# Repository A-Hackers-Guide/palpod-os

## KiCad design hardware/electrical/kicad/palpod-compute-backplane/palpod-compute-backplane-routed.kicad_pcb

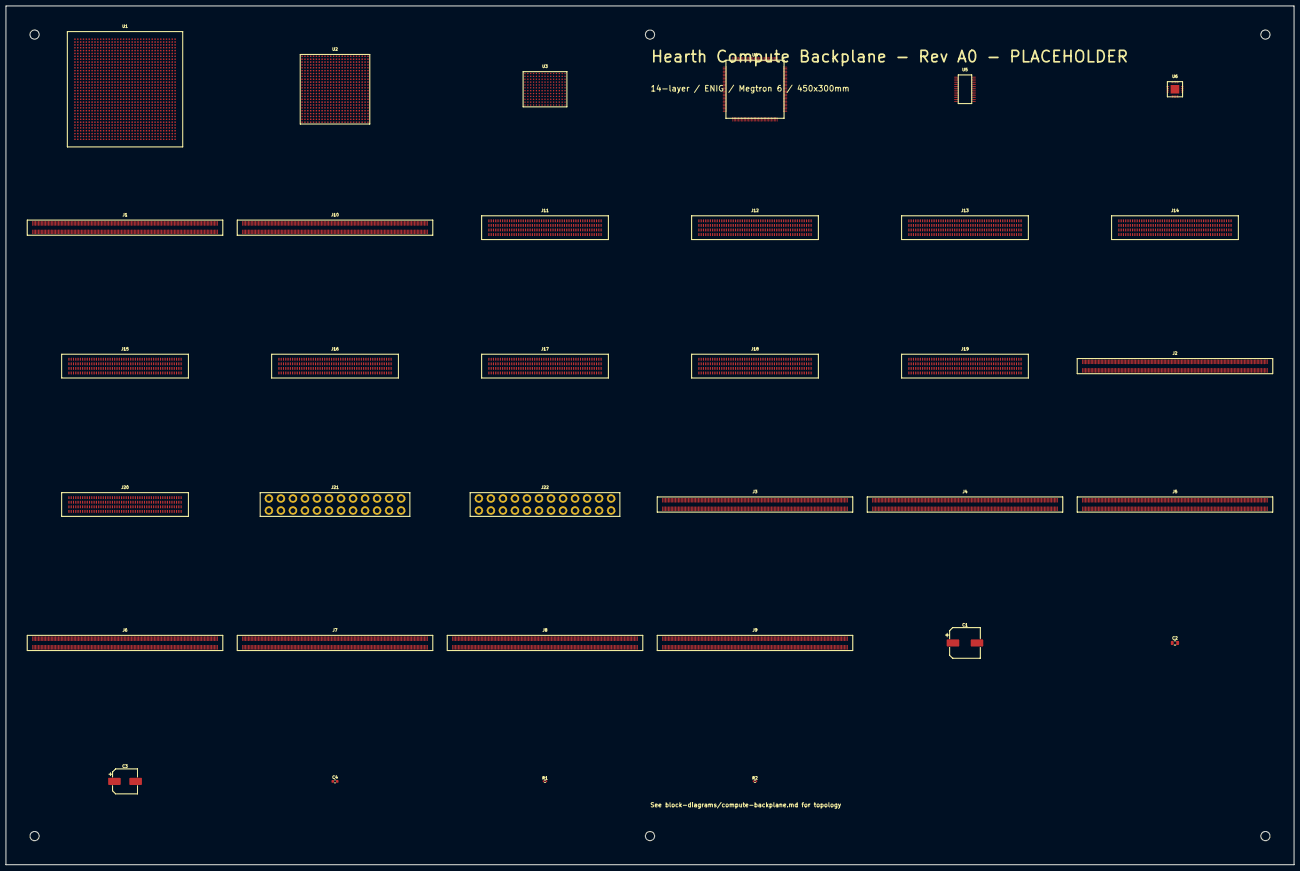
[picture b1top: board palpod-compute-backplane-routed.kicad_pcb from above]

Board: 14 copper layers, 450.0 x 300.0 mm, 34 parts (0 on the bottom side), 4 nets, no tracks yet.

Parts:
C1: 470uF/25V; CP_Elec_10x10.5
C2: 10uF/25V; C_0805_2012Metric
C3: 220uF/16V; CP_Elec_8x10.5
C4: 10uF/6.3V; C_0603_1608Metric
J1: MM70_260_SODIMM (Jetson Orin NX #0); MM70_260_SODIMM
J2: MM70_260_SODIMM (Jetson Orin NX #1); MM70_260_SODIMM
J3: MM70_260_SODIMM (Jetson Orin NX #2); MM70_260_SODIMM
J4: MM70_260_SODIMM (Jetson Orin NX #3); MM70_260_SODIMM
J5: MM70_260_SODIMM (Jetson Orin NX #4); MM70_260_SODIMM
J6: MM70_260_SODIMM (Jetson Orin NX #5); MM70_260_SODIMM
J7: MM70_260_SODIMM (Jetson Orin NX #6); MM70_260_SODIMM
J8: MM70_260_SODIMM (Jetson Orin NX #7); MM70_260_SODIMM
J9: MM70_260_SODIMM (Jetson Orin NX #8); MM70_260_SODIMM
J10: MM70_260_SODIMM (Jetson Orin NX #9); MM70_260_SODIMM
J11: SAMTEC_EXAMAX_200 (Ryzen AI 9 HX 370 #0); SAMTEC_EXAMAX_200
J12: SAMTEC_EXAMAX_200 (Ryzen AI 9 HX 370 #1); SAMTEC_EXAMAX_200
J13: SAMTEC_EXAMAX_200 (Ryzen AI 9 HX 370 #2); SAMTEC_EXAMAX_200
J14: SAMTEC_EXAMAX_200 (Ryzen AI 9 HX 370 #3); SAMTEC_EXAMAX_200
J15: SAMTEC_EXAMAX_200 (Ryzen AI 9 HX 370 #4); SAMTEC_EXAMAX_200
J16: SAMTEC_EXAMAX_200 (Ryzen AI 9 HX 370 #5); SAMTEC_EXAMAX_200
J17: SAMTEC_EXAMAX_200 (Ryzen AI 9 HX 370 #6); SAMTEC_EXAMAX_200
J18: SAMTEC_EXAMAX_200 (Ryzen AI 9 HX 370 #7); SAMTEC_EXAMAX_200
J19: SAMTEC_EXAMAX_200 (Ryzen AI 9 HX 370 #8); SAMTEC_EXAMAX_200
J20: SAMTEC_EXAMAX_200 (Ryzen AI 9 HX 370 #9); SAMTEC_EXAMAX_200
J21: ATX24 (+12V PSU input); ATX24_HEADER
J22: ATX24 (+12V PSU input B); ATX24_HEADER
R1: 10k; R_0402_1005Metric
R2: 3.3k; R_0402_1005Metric
U1: BCM56780 (Trident 4 12.8Tbps); BCM56780_HFCBGA1300
U2: ARIES_PT4 (PCIe Gen5 retimer); ARIES_PT4_BGA544
U3: UCD90320 (32-rail sequencer); UCD90320_BGA173
U4: NCT6116 (BMC / super-I/O); NCT6116_LQFP128
U5: SLB9670 (TPM 2.0); SLB9670_TSSOP28
U6: TPS543x (12V -> 5V, 15A); TPS543x_QFN

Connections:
GND: J1.1, J1.2, J1.129, J1.130, J1.135, J1.136, J1.259, J1.260
VCC: U3.76, U3.77, U3.78, U4.38, U4.39, U4.40, U4.41, U5.10
VDD: J1.33, J1.34, J1.35, J1.36, J1.131, J1.132, J1.133, J1.134
VIN: U6.1, U6.2

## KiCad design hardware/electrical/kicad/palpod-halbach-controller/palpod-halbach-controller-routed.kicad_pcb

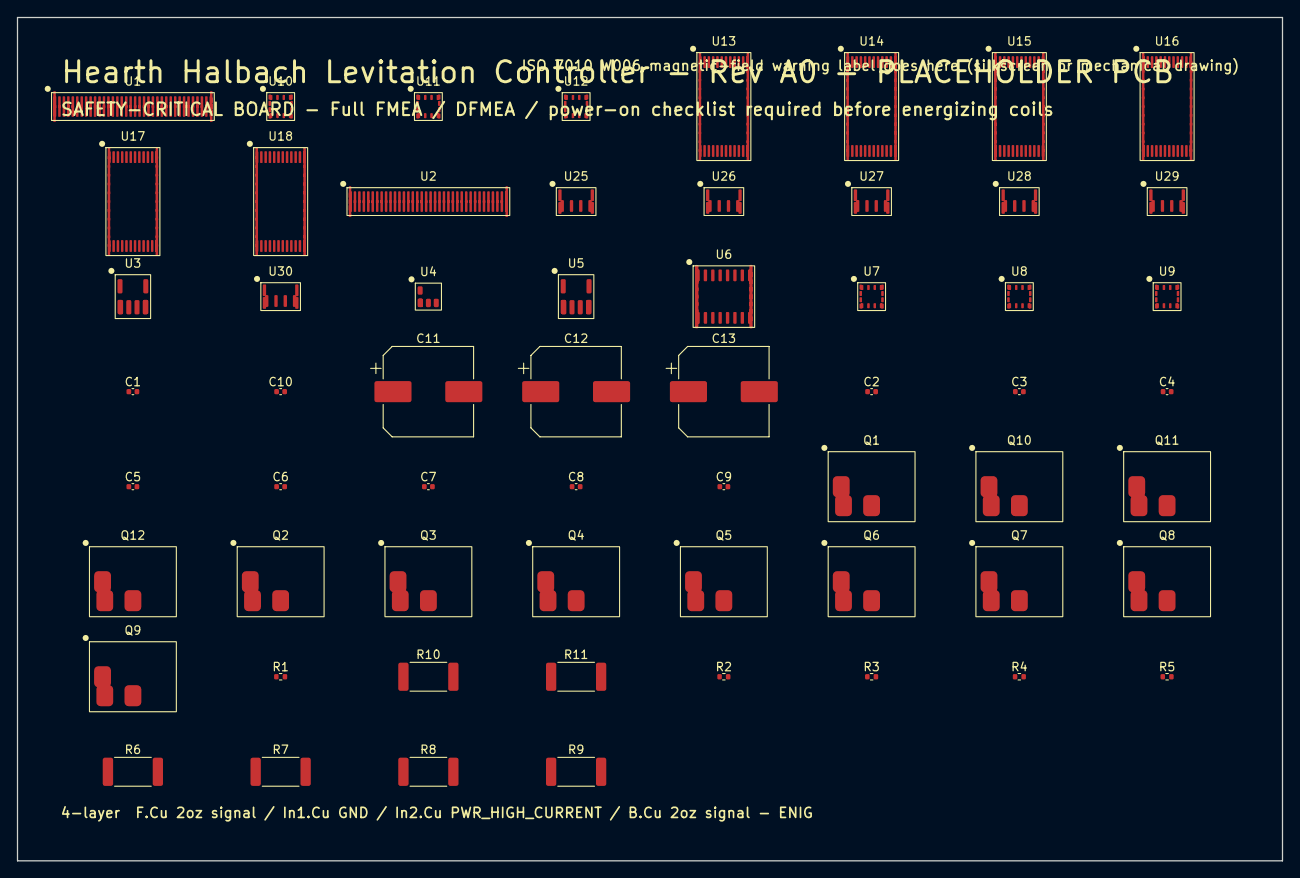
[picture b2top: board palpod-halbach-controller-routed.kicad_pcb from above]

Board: 4 copper layers, 150.0 x 100.0 mm, 60 parts (0 on the bottom side), 3 nets, no tracks yet.

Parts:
C1, C2, C3, C4, C5, C6, C7, C8, C9, C10: 100nF; C_0402_1005Metric
C11, C12, C13: 220uF; CP_Elec_10x10.5
Q1, Q2, Q3, Q4, Q5, Q6, Q7, Q8, Q9, Q10, Q11, Q12: IPI050N06N; TO-262-3_TabPin2
R1, R2, R3, R4, R5: 10k; R_0402_1005Metric
R6, R7, R8, R9, R10, R11: 0R005 5W; R_2512_6332Metric
U1: STM32H723ZGT6 (Primary); LQFP-144_20x20mm_P0.5mm
U2: STM32H723ZGT6 (Redundant); LQFP-144_20x20mm_P0.5mm
U3: MAX706; SOIC-8_3.9x4.9mm_P1.27mm
U4: TL331; SOT-23-5
U5: MCP2542FD; SOIC-8_3.9x4.9mm_P1.27mm
U6: STM32G030K8T6; LQFP-32_7x7mm_P0.8mm
U7: MLX90393 #1; QFN-16_3x3mm_P0.5mm
U8: MLX90393 #2; QFN-16_3x3mm_P0.5mm
U9: MLX90393 #3; QFN-16_3x3mm_P0.5mm
U10: MLX90393 #4; QFN-16_3x3mm_P0.5mm
U11: MLX90393 #5; QFN-16_3x3mm_P0.5mm
U12: MLX90393 #6; QFN-16_3x3mm_P0.5mm
U13: DRV8323 CH1; HTSSOP-48_6.1x12.5mm_P0.5mm_EP
U14: DRV8323 CH2; HTSSOP-48_6.1x12.5mm_P0.5mm_EP
U15: DRV8323 CH3; HTSSOP-48_6.1x12.5mm_P0.5mm_EP
U16: DRV8323 CH4; HTSSOP-48_6.1x12.5mm_P0.5mm_EP
U17: DRV8323 CH5; HTSSOP-48_6.1x12.5mm_P0.5mm_EP
U18: DRV8323 CH6; HTSSOP-48_6.1x12.5mm_P0.5mm_EP
U25, U26, U27, U28, U29, U30: INA240; TSSOP-8_4.4x3mm_P0.65mm

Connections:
GVDD: U13.40, U14.40, U15.40, U16.40, U17.40, U18.40
PVDD: U13.38, U14.38, U15.38, U16.38, U17.38, U18.38
V+: U4.5, U25.8, U26.8, U27.8, U28.8, U29.8, U30.8

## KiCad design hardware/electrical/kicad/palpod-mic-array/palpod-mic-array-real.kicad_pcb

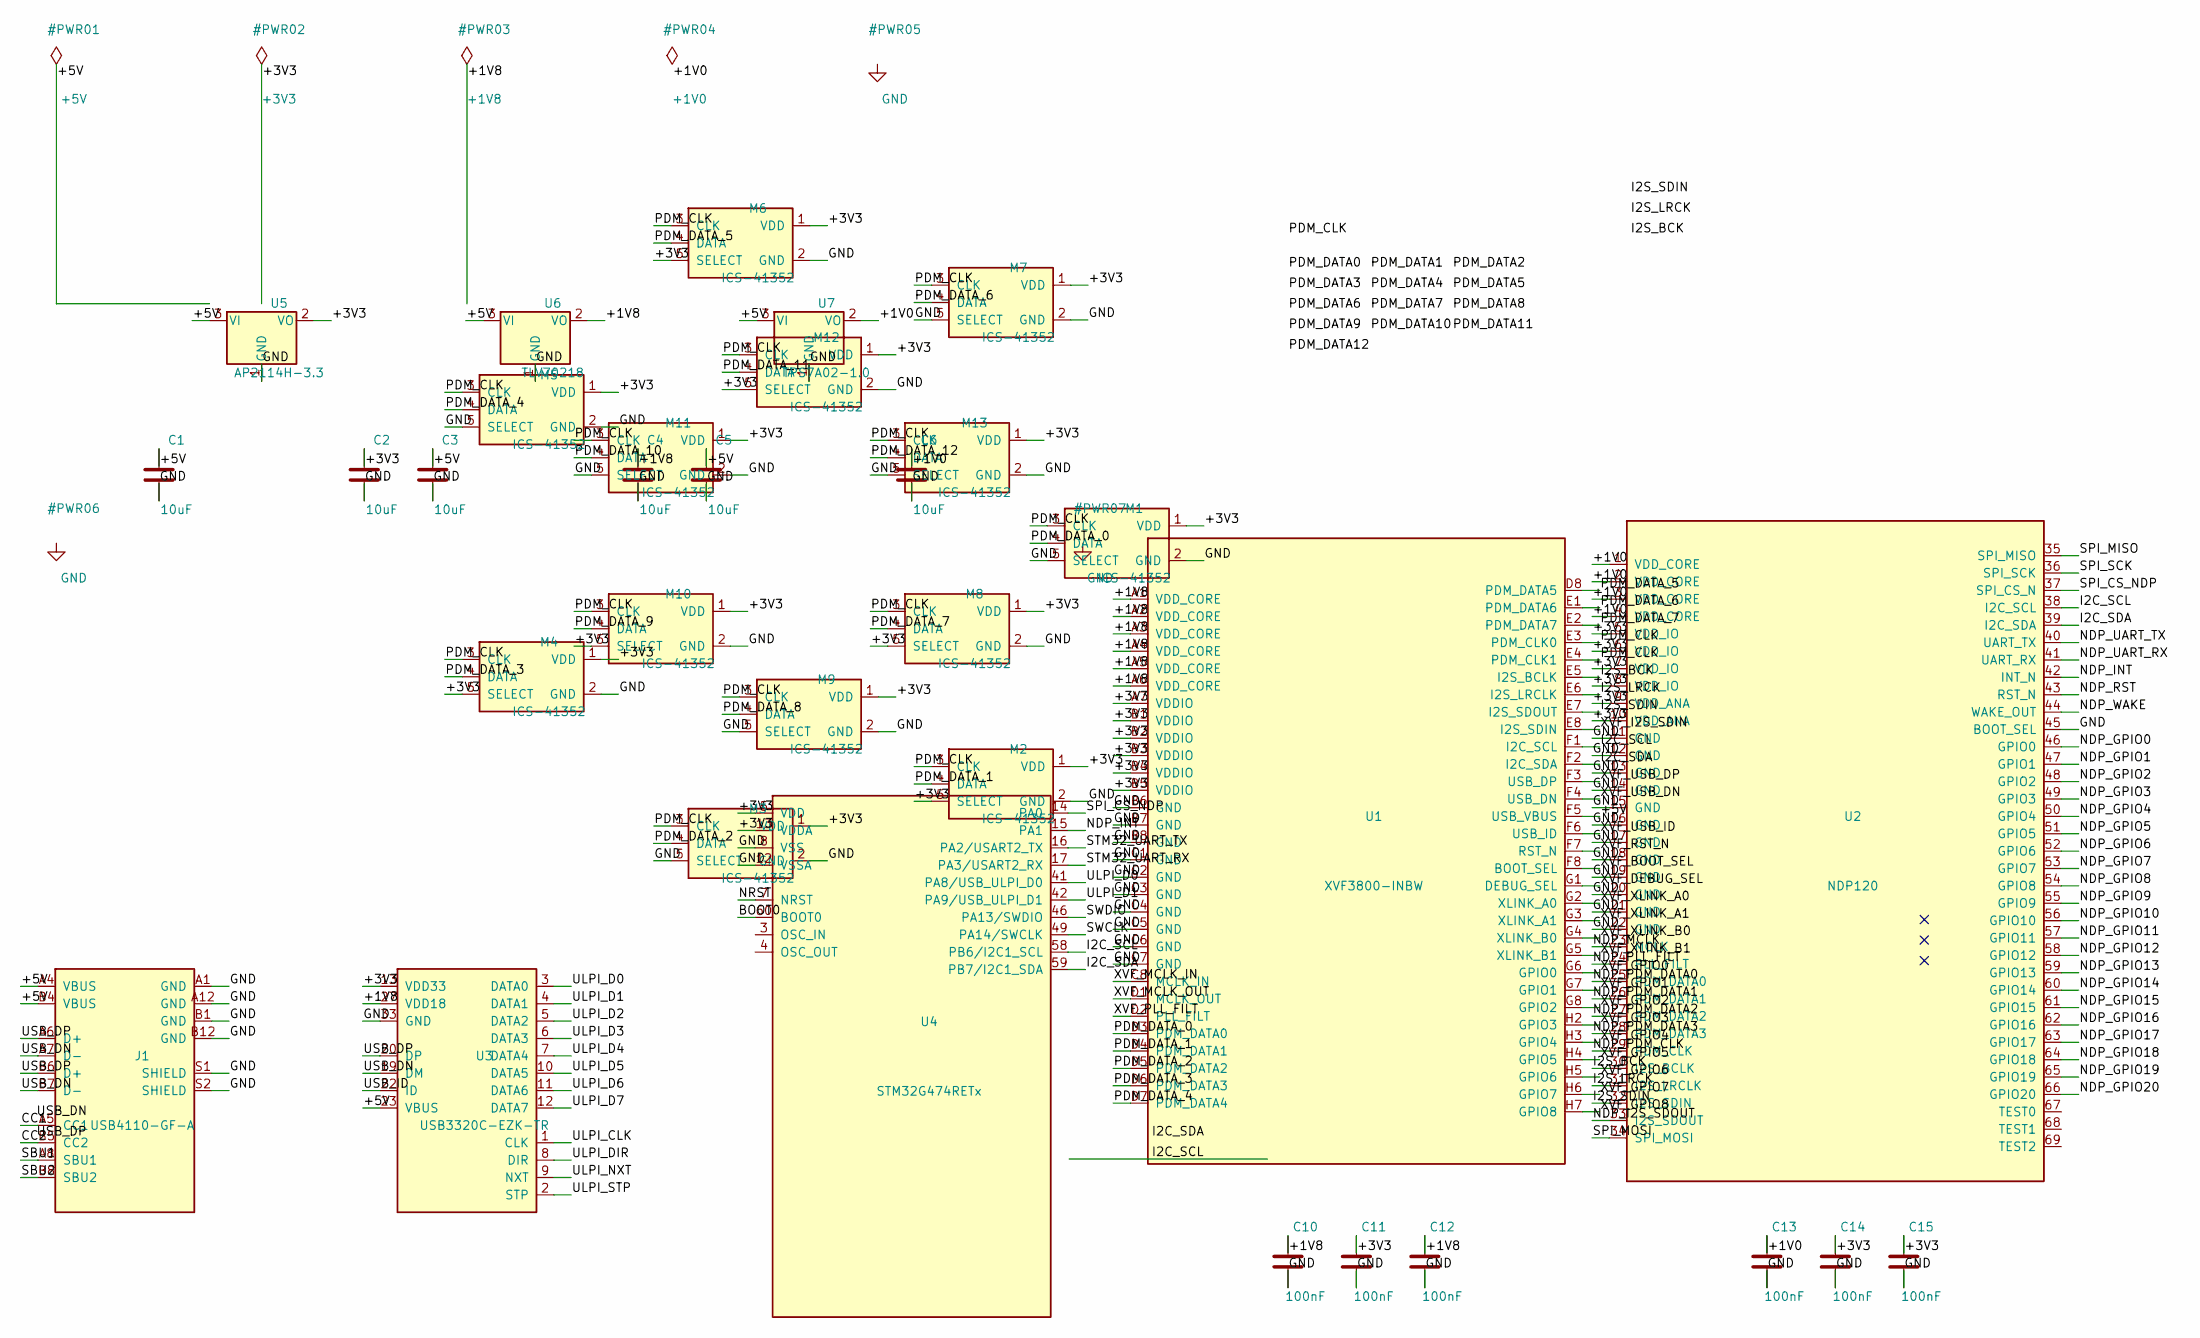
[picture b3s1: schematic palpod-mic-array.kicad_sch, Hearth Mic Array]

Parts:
C1, C2, C3, C4, C5, C6: 10uF; C_0603_1608Metric
C10, C11, C12, C13, C14, C15: 100nF; C_0402_1005Metric
J1: USB4110-GF-A; USB_C_Receptacle_GCT_USB4110-xx-A
M1, M2, M3, M4, M5, M6, M7, M8, M9, M10, M11, M12, M13: ICS-41352; ICS-41352_LGA5
U1: XVF3800-INBW; XVF3800_LFBGA61
U2: NDP120; NDP120_LGA69
U3: USB3320C-EZK-TR; QFN-32-1EP_5x5mm_P0.5mm_EP3.35x3.35mm
U4: STM32G474RETx; LQFP-64_10x10mm_P0.5mm
U5: AP2114H-3.3; SOT-223-3_TabPin2
U6: TLV70218; SOT-223-3_TabPin2
U7: TPS7A02-1.0; SOT-223-3_TabPin2

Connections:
+1V0: C6.1, C13.1, U2.1 (VDD_CORE), U2.2 (VDD_CORE), U2.3 (VDD_CORE), U2.4 (VDD_CORE), U7.2 (VO)
+1V8: C4.1, C10.1, C12.1, U1.A1 (VDD_CORE), U1.A2 (VDD_CORE), U1.A3 (VDD_CORE), U1.A4 (VDD_CORE), U1.A5 (VDD_CORE), U1.A6 (VDD_CORE), U3.27 (VDD18), U6.2 (VO)
+3V3: C2.1, C11.1, C14.1, C15.1, M1.1 (VDD), M2.1 (VDD), M2.5 (SELECT), M3.1 (VDD), M4.1 (VDD), M4.5 (SELECT), M5.1 (VDD), M6.1 (VDD), M6.5 (SELECT), M7.1 (VDD), M8.1 (VDD), M8.5 (SELECT), M9.1 (VDD), M10.1 (VDD), M10.5 (SELECT), M11.1 (VDD), M12.1 (VDD), M12.5 (SELECT), M13.1 (VDD), U1.A7 (VDDIO), U1.B1 (VDDIO), U1.B2 (VDDIO), U1.B3 (VDDIO), U1.B4 (VDDIO), U1.B5 (VDDIO), U2.5 (VDD_IO), U2.6 (VDD_IO), U2.7 (VDD_IO), U2.8 (VDD_IO), U2.9 (VDD_ANA), U2.10 (VDD_ANA), U3.13 (VDD33), U4.5 (VDD), U4.13 (VDDA), U5.2 (VO)
+5V: C1.1, C3.1, C5.1, J1.A4 (VBUS), J1.B4 (VBUS), U1.F5 (USB_VBUS), U3.23 (VBUS), U5.3 (VI), U6.3 (VI), U7.3 (VI)
BOOT0: U4.60 (BOOT0)
CC1: J1.A5 (CC1)
CC2: J1.B5 (CC2)
GND: C1.2, C2.2, C3.2, C4.2, C5.2, C6.2, C10.2, C11.2, C12.2, C13.2, C14.2, C15.2, J1.A1 (GND), J1.A12 (GND), J1.B1 (GND), J1.B12 (GND), J1.S1 (SHIELD), J1.S2 (SHIELD), M1.2 (GND), M1.5 (SELECT), M2.2 (GND), M3.2 (GND), M3.5 (SELECT), M4.2 (GND), M5.2 (GND), M5.5 (SELECT), M6.2 (GND), M7.2 (GND), M7.5 (SELECT), M8.2 (GND), M9.2 (GND), M9.5 (SELECT), M10.2 (GND), M11.2 (GND), M11.5 (SELECT), M12.2 (GND), M13.2 (GND), M13.5 (SELECT), U1.B6 (GND), U1.B7 (GND), U1.B8 (GND), U1.C1 (GND), U1.C2 (GND), U1.C3 (GND), U1.C4 (GND), U1.C5 (GND), U1.C6 (GND), U1.C7 (GND), U2.11 (GND), U2.12 (GND), U2.13 (GND), U2.14 (GND), U2.15 (GND), U2.16 (GND), U2.17 (GND), U2.18 (GND), U2.19 (GND), U2.20 (GND), U2.21 (GND), U2.22 (GND), U2.45 (BOOT_SEL), U3.33 (GND), U4.8 (VSS), U4.12 (VSSA), U5.1 (GND), U6.1 (GND), U7.1 (GND)
I2C_SCL: U1.F1 (I2C_SCL), U2.38 (I2C_SCL), U4.58 (PB6/I2C1_SCL)
I2C_SDA: U1.F2 (I2C_SDA), U2.39 (I2C_SDA), U4.59 (PB7/I2C1_SDA)
I2S_BCK: U1.E5 (I2S_BCLK), U2.30 (I2S_BCLK)
I2S_LRCK: U1.E6 (I2S_LRCLK), U2.31 (I2S_LRCLK)
I2S_SDIN: U1.E7 (I2S_SDOUT), U2.32 (I2S_SDIN)
NDP_GPIO0: U2.46 (GPIO0)
NDP_GPIO1: U2.47 (GPIO1)
NDP_GPIO2: U2.48 (GPIO2)
NDP_GPIO3: U2.49 (GPIO3)
NDP_GPIO4: U2.50 (GPIO4)
NDP_GPIO5: U2.51 (GPIO5)
NDP_GPIO6: U2.52 (GPIO6)
NDP_GPIO7: U2.53 (GPIO7)
NDP_GPIO8: U2.54 (GPIO8)
NDP_GPIO9: U2.55 (GPIO9)
NDP_GPIO10: U2.56 (GPIO10)
NDP_GPIO11: U2.57 (GPIO11)
NDP_GPIO12: U2.58 (GPIO12)
NDP_GPIO13: U2.59 (GPIO13)
NDP_GPIO14: U2.60 (GPIO14)
NDP_GPIO15: U2.61 (GPIO15)
NDP_GPIO16: U2.62 (GPIO16)
NDP_GPIO17: U2.63 (GPIO17)
NDP_GPIO18: U2.64 (GPIO18)
NDP_GPIO19: U2.65 (GPIO19)
NDP_GPIO20: U2.66 (GPIO20)
NDP_I2S_SDOUT: U2.33 (I2S_SDOUT)
NDP_INT: U2.42 (INT_N), U4.15 (PA1)
NDP_MCLK: U2.23 (MCLK)
NDP_PDM_CLK: U2.29 (PDM_CLK)
NDP_PDM_DATA0: U2.25 (PDM_DATA0)
NDP_PDM_DATA1: U2.26 (PDM_DATA1)
NDP_PDM_DATA2: U2.27 (PDM_DATA2)
NDP_PDM_DATA3: U2.28 (PDM_DATA3)
NDP_PLL_FILT: U2.24 (PLL_FILT)
NDP_RST: U2.43 (RST_N)
NDP_UART_RX: U2.41 (UART_RX)
NDP_UART_TX: U2.40 (UART_TX)
NDP_WAKE: U2.44 (WAKE_OUT)
NRST: U4.7 (NRST)
PDM_CLK: M1.3 (CLK), M2.3 (CLK), M3.3 (CLK), M4.3 (CLK), M5.3 (CLK), M6.3 (CLK), M7.3 (CLK), M8.3 (CLK), M9.3 (CLK), M10.3 (CLK), M11.3 (CLK), M12.3 (CLK), M13.3 (CLK), U1.E3 (PDM_CLK0), U1.E4 (PDM_CLK1)
PDM_DATA_0: M1.4 (DATA), U1.D3 (PDM_DATA0)
PDM_DATA_1: M2.4 (DATA), U1.D4 (PDM_DATA1)
PDM_DATA_2: M3.4 (DATA), U1.D5 (PDM_DATA2)
PDM_DATA_3: M4.4 (DATA), U1.D6 (PDM_DATA3)
PDM_DATA_4: M5.4 (DATA), U1.D7 (PDM_DATA4)
PDM_DATA_5: M6.4 (DATA), U1.D8 (PDM_DATA5)
PDM_DATA_6: M7.4 (DATA), U1.E1 (PDM_DATA6)
PDM_DATA_7: M8.4 (DATA), U1.E2 (PDM_DATA7)
PDM_DATA_8: M9.4 (DATA)
PDM_DATA_9: M10.4 (DATA)
PDM_DATA_10: M11.4 (DATA)
PDM_DATA_11: M12.4 (DATA)
PDM_DATA_12: M13.4 (DATA)
SBU1: J1.A8 (SBU1)
SBU2: J1.B8 (SBU2)
SPI_CS_NDP: U2.37 (SPI_CS_N), U4.14 (PA0)
SPI_MISO: U2.35 (SPI_MISO)
SPI_MOSI: U2.34 (SPI_MOSI)
SPI_SCK: U2.36 (SPI_SCK)
STM32_UART_RX: U4.17 (PA3/USART2_RX)
STM32_UART_TX: U4.16 (PA2/USART2_TX)
SWCLK: U4.49 (PA14/SWCLK)
SWDIO: U4.46 (PA13/SWDIO)
ULPI_CLK: U3.1 (CLK)
ULPI_D0: U3.3 (DATA0), U4.41 (PA8/USB_ULPI_D0)
ULPI_D1: U3.4 (DATA1), U4.42 (PA9/USB_ULPI_D1)
ULPI_D2: U3.5 (DATA2)
ULPI_D3: U3.6 (DATA3)
ULPI_D4: U3.7 (DATA4)
ULPI_D5: U3.10 (DATA5)
ULPI_D6: U3.11 (DATA6)
ULPI_D7: U3.12 (DATA7)
ULPI_DIR: U3.8 (DIR)
ULPI_NXT: U3.9 (NXT)
ULPI_STP: U3.2 (STP)
USB_DN: J1.A7 (D-), J1.B7 (D-), U3.19 (DM)
USB_DP: J1.A6 (D+), J1.B6 (D+), U3.20 (DP)
USB_ID: U3.22 (ID)
XVF_BOOT_SEL: U1.F8 (BOOT_SEL)
XVF_DEBUG_SEL: U1.G1 (DEBUG_SEL)
XVF_GPIO0: U1.G6 (GPIO0)
XVF_GPIO1: U1.G7 (GPIO1)
XVF_GPIO2: U1.G8 (GPIO2)
XVF_GPIO3: U1.H2 (GPIO3)
XVF_GPIO4: U1.H3 (GPIO4)
XVF_GPIO5: U1.H4 (GPIO5)
XVF_GPIO6: U1.H5 (GPIO6)
XVF_GPIO7: U1.H6 (GPIO7)
XVF_GPIO8: U1.H7 (GPIO8)
XVF_I2S_SDIN: U1.E8 (I2S_SDIN)
XVF_MCLK_IN: U1.C8 (MCLK_IN)
XVF_MCLK_OUT: U1.D1 (MCLK_OUT)
XVF_PLL_FILT: U1.D2 (PLL_FILT)
XVF_RST_N: U1.F7 (RST_N)
XVF_USB_DN: U1.F4 (USB_DN)
XVF_USB_DP: U1.F3 (USB_DP)
XVF_USB_ID: U1.F6 (USB_ID)
XVF_XLINK_A0: U1.G2 (XLINK_A0)
XVF_XLINK_A1: U1.G3 (XLINK_A1)
XVF_XLINK_B0: U1.G4 (XLINK_B0)
XVF_XLINK_B1: U1.G5 (XLINK_B1)

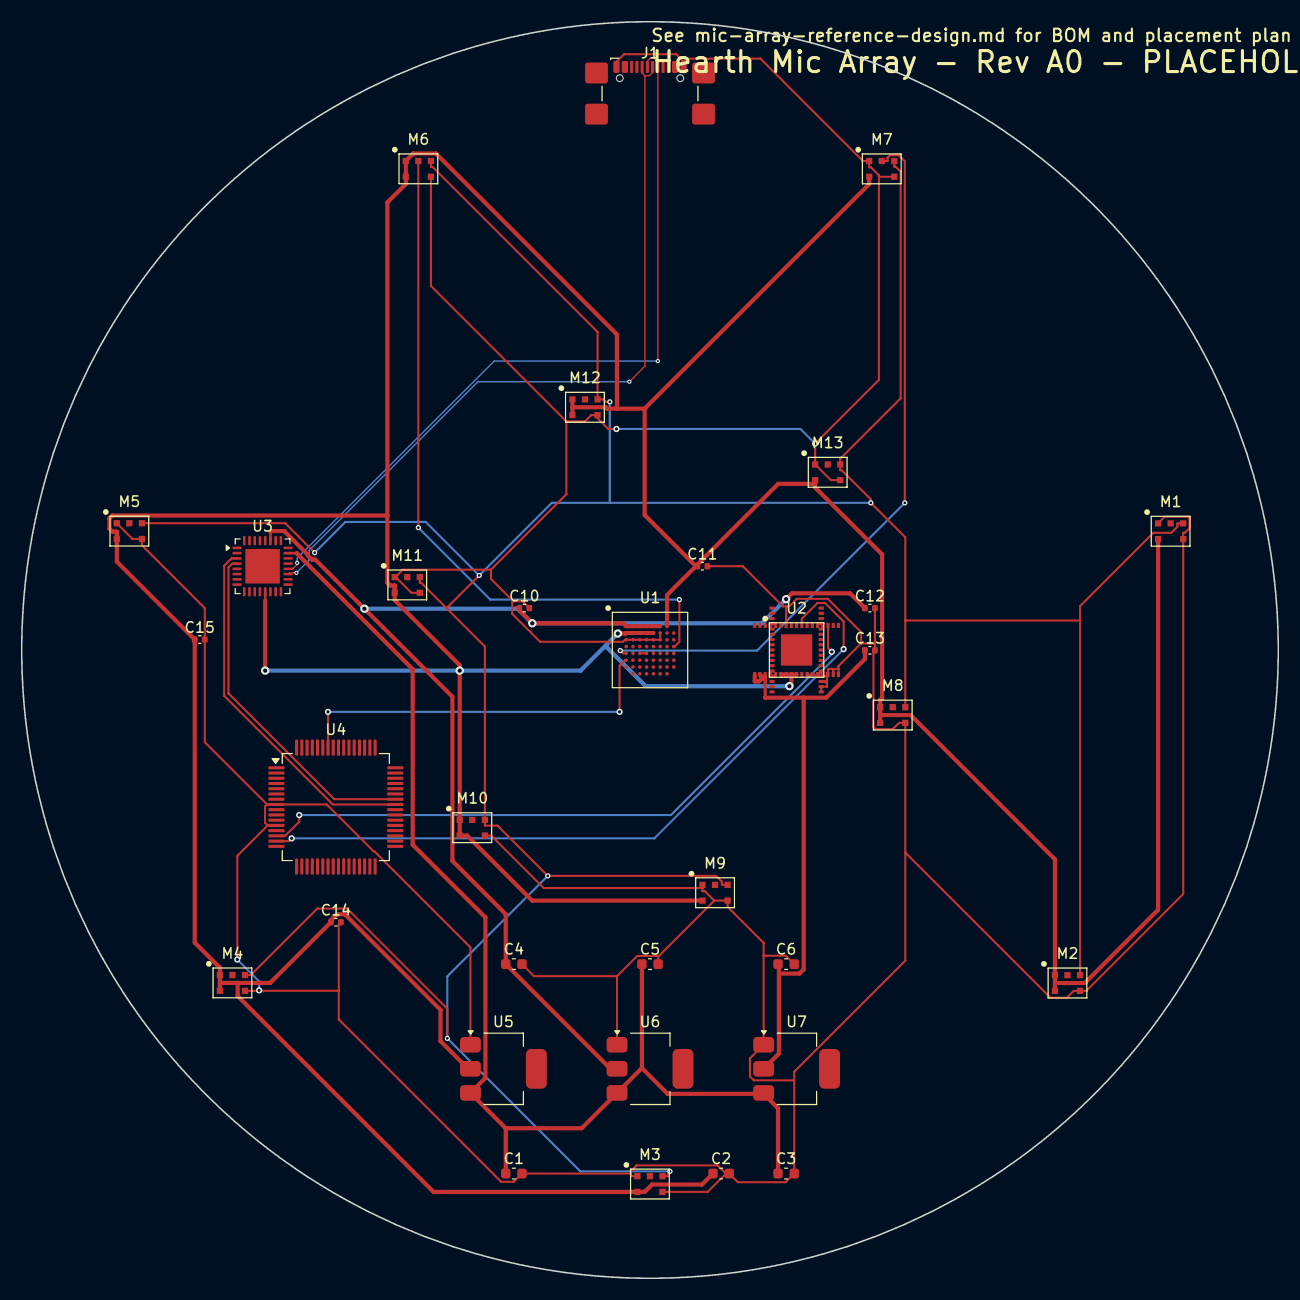
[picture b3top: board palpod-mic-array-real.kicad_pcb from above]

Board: 4 copper layers, 120.0 x 120.0 mm, 33 parts (0 on the bottom side), 25 nets.

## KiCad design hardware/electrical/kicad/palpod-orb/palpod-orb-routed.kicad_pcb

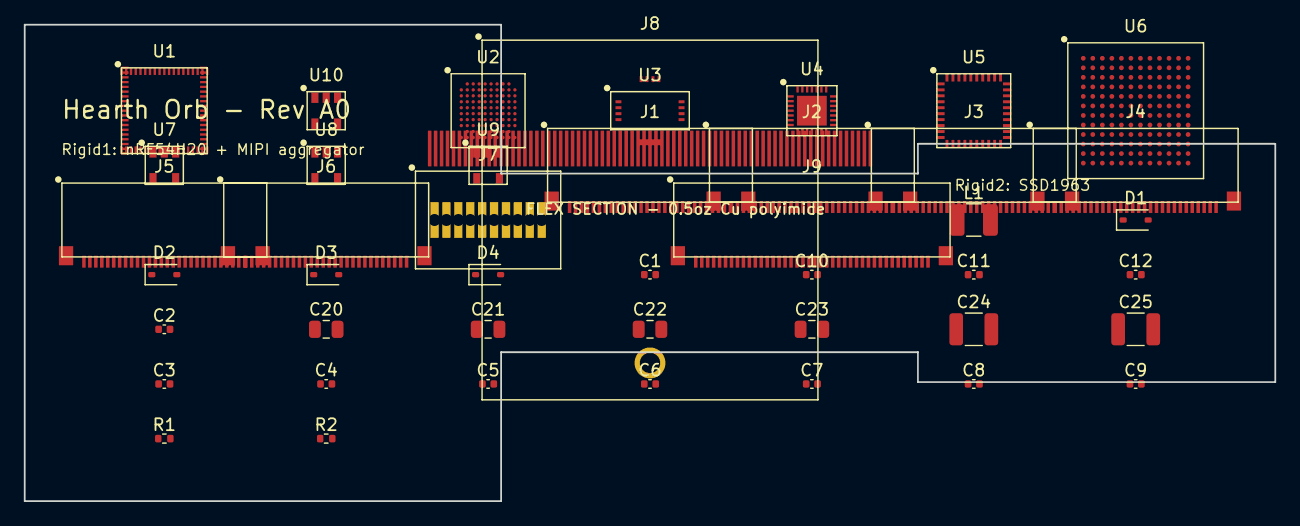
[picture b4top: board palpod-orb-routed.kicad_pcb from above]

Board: 6 copper layers, 105.0 x 40.0 mm, 44 parts (0 on the bottom side), 6 nets, no tracks yet.

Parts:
C1, C2, C3, C4, C5, C6, C7, C8, C9, C10, C11, C12: 100nF; C_0402_1005Metric
C20, C21, C22, C23: 10uF; C_0805_2012Metric
C24: 22uF; C_1210_3225Metric
C25: 220uF; C_1210_3225Metric
D1, D2, D3, D4: PMEG3020; D_SOD-323
J1: IMX415_CAM1; FPC28_0.5mm_ZIF
J2: IMX415_CAM2; FPC28_0.5mm_ZIF
J3: IMX415_CAM3; FPC28_0.5mm_ZIF
J4: IMX415_CAM4; FPC28_0.5mm_ZIF
J5: IMX415_CAM5; FPC28_0.5mm_ZIF
J6: IMX415_CAM6; FPC28_0.5mm_ZIF
J7: S3_LIDAR; S3_LIDAR_UART10
J8: WiFi7_M2; M2_2230_KeyAE
J9: OLED_OUT; FPC40_0.5mm_ZIF
L1: 10uH; L_1210_3225Metric
R1, R2: 4.7k; R_0402_1005Metric
U1: nRF54H20; nRF54H20_aQFN94
U2: TC358748; TC358748_BGA80
U3: VL53L8; VL53L8_LGA16
U4: BQ25798; BQ25798_QFN29
U5: P9418; P9418_QFN40
U6: SSD1963; SSD1963_LFBGA121
U7, U8, U9, U10: TMR2305; TMR2305_SOT23-5

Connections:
3V3: J8.6, J8.8, J8.72, J8.74
AVDD: U3.1, U3.2
GND: J1.3, J1.6, J1.9, J1.12, J1.15, J1.18, J1.27, J2.3
VBUS: U4.1, U4.2
VCC: J7.1, U7.1, U8.1, U9.1, U10.1
VDD: J1.24, J1.25, J1.26, J2.24, J2.25, J2.26, J3.24, J3.26

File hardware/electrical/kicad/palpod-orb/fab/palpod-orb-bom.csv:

"Refs","Value","Footprint","Qty","DNP"
"C1","100nF","Capacitor_SMD:C_0402_1005Metric","1",""
"C2","100nF","Capacitor_SMD:C_0402_1005Metric","1",""
"C3","100nF","Capacitor_SMD:C_0402_1005Metric","1",""
"C4","100nF","Capacitor_SMD:C_0402_1005Metric","1",""
"C5","100nF","Capacitor_SMD:C_0402_1005Metric","1",""
"C6","100nF","Capacitor_SMD:C_0402_1005Metric","1",""
"C7","100nF","Capacitor_SMD:C_0402_1005Metric","1",""
"C8","100nF","Capacitor_SMD:C_0402_1005Metric","1",""
"C9","100nF","Capacitor_SMD:C_0402_1005Metric","1",""
"C10","100nF","Capacitor_SMD:C_0402_1005Metric","1",""
"C11","100nF","Capacitor_SMD:C_0402_1005Metric","1",""
"C12","100nF","Capacitor_SMD:C_0402_1005Metric","1",""
"C20","10uF","Capacitor_SMD:C_0805_2012Metric","1",""
"C21","10uF","Capacitor_SMD:C_0805_2012Metric","1",""
"C22","10uF","Capacitor_SMD:C_0805_2012Metric","1",""
"C23","10uF","Capacitor_SMD:C_0805_2012Metric","1",""
"C24","22uF","Capacitor_SMD:C_1210_3225Metric","1",""
"C25","220uF","Capacitor_SMD:C_1210_3225Metric","1",""
"D1","PMEG3020","Diode_SMD:D_SOD-323","1",""
"D2","PMEG3020","Diode_SMD:D_SOD-323","1",""
"D3","PMEG3020","Diode_SMD:D_SOD-323","1",""
"D4","PMEG3020","Diode_SMD:D_SOD-323","1",""
"J1","IMX415_CAM1","palpod-orb:FPC28_0.5mm_ZIF","1",""
"J2","IMX415_CAM2","palpod-orb:FPC28_0.5mm_ZIF","1",""
"J3","IMX415_CAM3","palpod-orb:FPC28_0.5mm_ZIF","1",""
"J4","IMX415_CAM4","palpod-orb:FPC28_0.5mm_ZIF","1",""
"J5","IMX415_CAM5","palpod-orb:FPC28_0.5mm_ZIF","1",""
"J6","IMX415_CAM6","palpod-orb:FPC28_0.5mm_ZIF","1",""
"J7","S3_LIDAR","palpod-orb:S3_LIDAR_UART10","1",""
"J8","WiFi7_M2","palpod-orb:M2_2230_KeyAE","1",""
"J9","OLED_OUT","palpod-orb:FPC40_0.5mm_ZIF","1",""
"L1","10uH","Inductor_SMD:L_1210_3225Metric","1",""
"R1","4.7k","Resistor_SMD:R_0402_1005Metric","1",""
"R2","4.7k","Resistor_SMD:R_0402_1005Metric","1",""
"U1","nRF54H20","palpod-orb:nRF54H20_aQFN94","1",""
"U2","TC358748","palpod-orb:TC358748_BGA80","1",""
"U3","VL53L8","palpod-orb:VL53L8_LGA16","1",""
"U4","BQ25798","palpod-orb:BQ25798_QFN29","1",""
"U5","P9418","palpod-orb:P9418_QFN40","1",""
"U6","SSD1963","palpod-orb:SSD1963_LFBGA121","1",""
"U7","TMR2305","palpod-orb:TMR2305_SOT23-5","1",""
"U8","TMR2305","palpod-orb:TMR2305_SOT23-5","1",""
"U9","TMR2305","palpod-orb:TMR2305_SOT23-5","1",""
"U10","TMR2305","palpod-orb:TMR2305_SOT23-5","1",""

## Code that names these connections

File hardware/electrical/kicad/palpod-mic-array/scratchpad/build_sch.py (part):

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    pins += sym_def_pin("input","line",-22.86,20.32,0,2.54,"BOOT0","60")
    pins += sym_def_pin("input","line",-22.86,17.78,0,2.54,"OSC_IN","3")
    pins += sym_def_pin("output","line",-22.86,15.24,0,2.54,"OSC_OUT","4")
    pins += sym_def_pin("bidirectional","line",22.86,35.56,180,2.54,"PA0","14")
    pins += sym_def_pin("bidirectional","line",22.86,33.02,180,2.54,"PA1","15")
    pins += sym_def_pin("bidirectional","line",22.86,30.48,180,2.54,"PA2/USART2_TX","16")
    pins += sym_def_pin("bidirectional","line",22.86,27.94,180,2.54,"PA3/USART2_RX","17")
    pins += sym_def_pin("bidirectional","line",22.86,25.4,180,2.54,"PA8/USB_ULPI_D0","41")
    pins += sym_def_pin("bidirectional","line",22.86,22.86,180,2.54,"PA9/USB_ULPI_D1","42")
    pins += sym_def_pin("bidirectional","line",22.86,20.32,180,2.54,"PA13/SWDIO","46")
    pins += sym_def_pin("bidirectional","line",22.86,17.78,180,2.54,"PA14/SWCLK","49")
    pins += sym_def_pin("bidirectional","line",22.86,15.24,180,2.54,"PB6/I2C1_SCL","58")
    pins += sym_def_pin("bidirectional","line",22.86,12.7,180,2.54,"PB7/I2C1_SDA","59")
    return f'''\t\t(symbol "MCU_ST_STM32G4:STM32G474RETx"
\t\t\t(pin_names
\t\t\t\t(offset 1.016)
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sch.append(label("+3V3", 60, 32, 0, "lbl-33"))
sch.append(label("+1V8", 90, 32, 0, "lbl-18"))
sch.append(label("+1V0", 120, 32, 0, "lbl-10"))
sch.append(label("I2C_SCL", 190, 190, 0, "lbl-scl"))
sch.append(label("I2C_SDA", 190, 187, 0, "lbl-sda"))
sch.append(label("USB_DP", 27, 187, 0, "lbl-dp"))
sch.append(label("USB_DN", 27, 184, 0, "lbl-dn"))
for i in range(13):
    sch.append(label(f"PDM_DATA{i}", 210 + (i % 3) * 12, 60 + (i // 3) * 3, 0, f"lbl-pdm{i}"))
sch.append(label("PDM_CLK", 210, 55, 0, "lbl-pdmclk"))
sch.append(label("I2S_BCK", 260, 55, 0, "lbl-i2sbck"))
sch.append(label("I2S_LRCK", 260, 52, 0, "lbl-i2slrck"))
sch.append(label("I2S_SDIN", 260, 49, 0, "lbl-i2ssdin"))

# --- no-connects on NDP test pins ---
sch.append(noconn(303, 155, "nc-test0"))
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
